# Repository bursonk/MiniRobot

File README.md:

# MiniRobot Design

A mini robot built within sumo robot specifications designed to push blocks outside of the ring.  Built to run autonomous or remotely controlled with Bluetooth, as well as a programmable OLED display for debugging.

## Table of contents
* [General info](#general-info)
* [Technologies](#technologies)
* [Project Status](#project-status)
* [Features](#features)
* [acknowledgements](#acknowledgements)

## General info
This project contains the custom chassis and PCB design files I created for a University Design Project in February 2020. 

## Technologies
* Teensy3.6
* KiCad
* SolidWorks

## Project Status
Due to various manufactures of component boards, location of mounting holes may need to be altered.

### To Do List
- [x] Update files to reflect final design
- [ ] Complete Project Documentation

## Features
The sumo robot features a 10cm X 10cm Chassis.

### Chassis

#### 3D printing

#### Threaded Inserts

### PCB

#### Soldering

#### Wiring and Connections

### Components

### Results

## Acknowledgements
A folder of SolidWorks parts with the electrical components used in the robot is included in this repository. 
Parts in this folder are used for the robot assembly design and were obtained from SolidWorks resources, from the manufacturer, or developed by me.

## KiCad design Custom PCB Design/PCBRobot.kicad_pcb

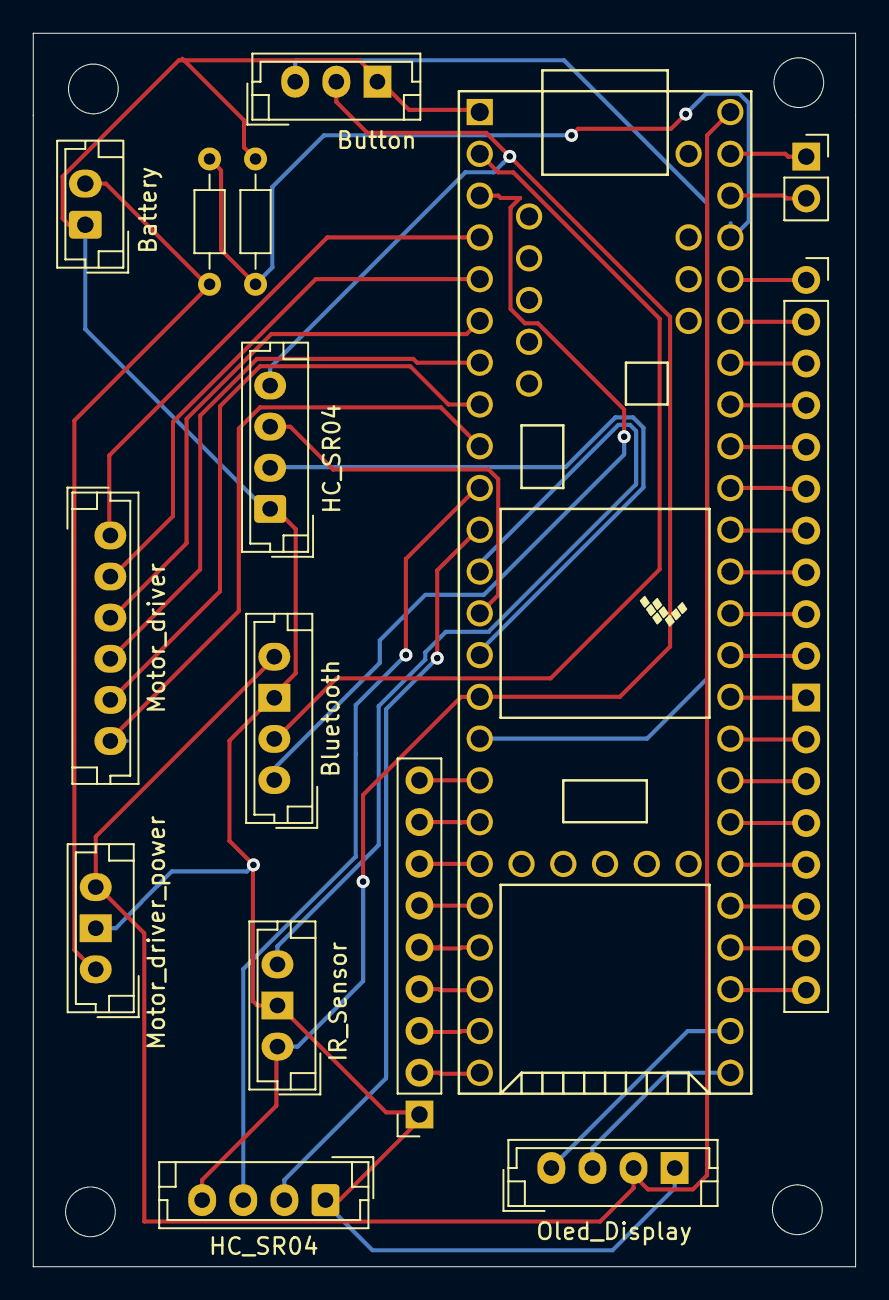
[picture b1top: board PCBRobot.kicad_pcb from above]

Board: 2 copper layers, 50.0 x 75.0 mm, 9 parts (0 on the bottom side), 4 nets.

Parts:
Battery: JST_EH_B2B-EH-A_1x02_P2.50mm_Vertical
Bluetooth: JST_EH_B4B-EH-A_1x04_P2.50mm_Vertical
Button: JST_EH_B3B-EH-A_1x03_P2.50mm_Vertical
HC_SR04, HC_SR04#2: JST_EH_B4B-EH-A_1x04_P2.50mm_Vertical
IR_Sensor: JST_EH_B3B-EH-A_1x03_P2.50mm_Vertical
Motor_driver: JST_EH_B6B-EH-A_1x06_P2.50mm_Vertical
Motor_driver_power: JST_EH_B3B-EH-A_1x03_P2.50mm_Vertical
Oled_Display: JST_EH_B4B-EH-A_1x04_P2.50mm_Vertical

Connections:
unnamed: Bluetooth.VCC, Motor_driver_power.+5V, Oled_Display.VCC
unnamed: Battery.-, Bluetooth.GND, Button.GND, HC_SR04.GND, HC_SR04#2.GND, IR_Sensor.GND, Motor_driver_power.GND, Oled_Display.GND
unnamed: Button.VCC, HC_SR04.VCC, HC_SR04#2.VCC, IR_Sensor.VCC
unnamed: Battery.+, Motor_driver_power.+12V

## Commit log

2021-07-05 Robot SolidWorks Files
    Custom Built from Scratch module robot design. Initial File Upload.
2021-07-05 PCB Design
    Adding custom PCB teensy shield design for components
2021-11-02 Add files via upload
    Updating to reflect Chassis Design
2021-11-02 Robot SolidWorks Files
    Updating files to reflect final project results
2021-11-02 Robot Design Files
    Updating to reflect final Robot design
2021-11-02 Robot Design Files
2021-11-02 Example Images
